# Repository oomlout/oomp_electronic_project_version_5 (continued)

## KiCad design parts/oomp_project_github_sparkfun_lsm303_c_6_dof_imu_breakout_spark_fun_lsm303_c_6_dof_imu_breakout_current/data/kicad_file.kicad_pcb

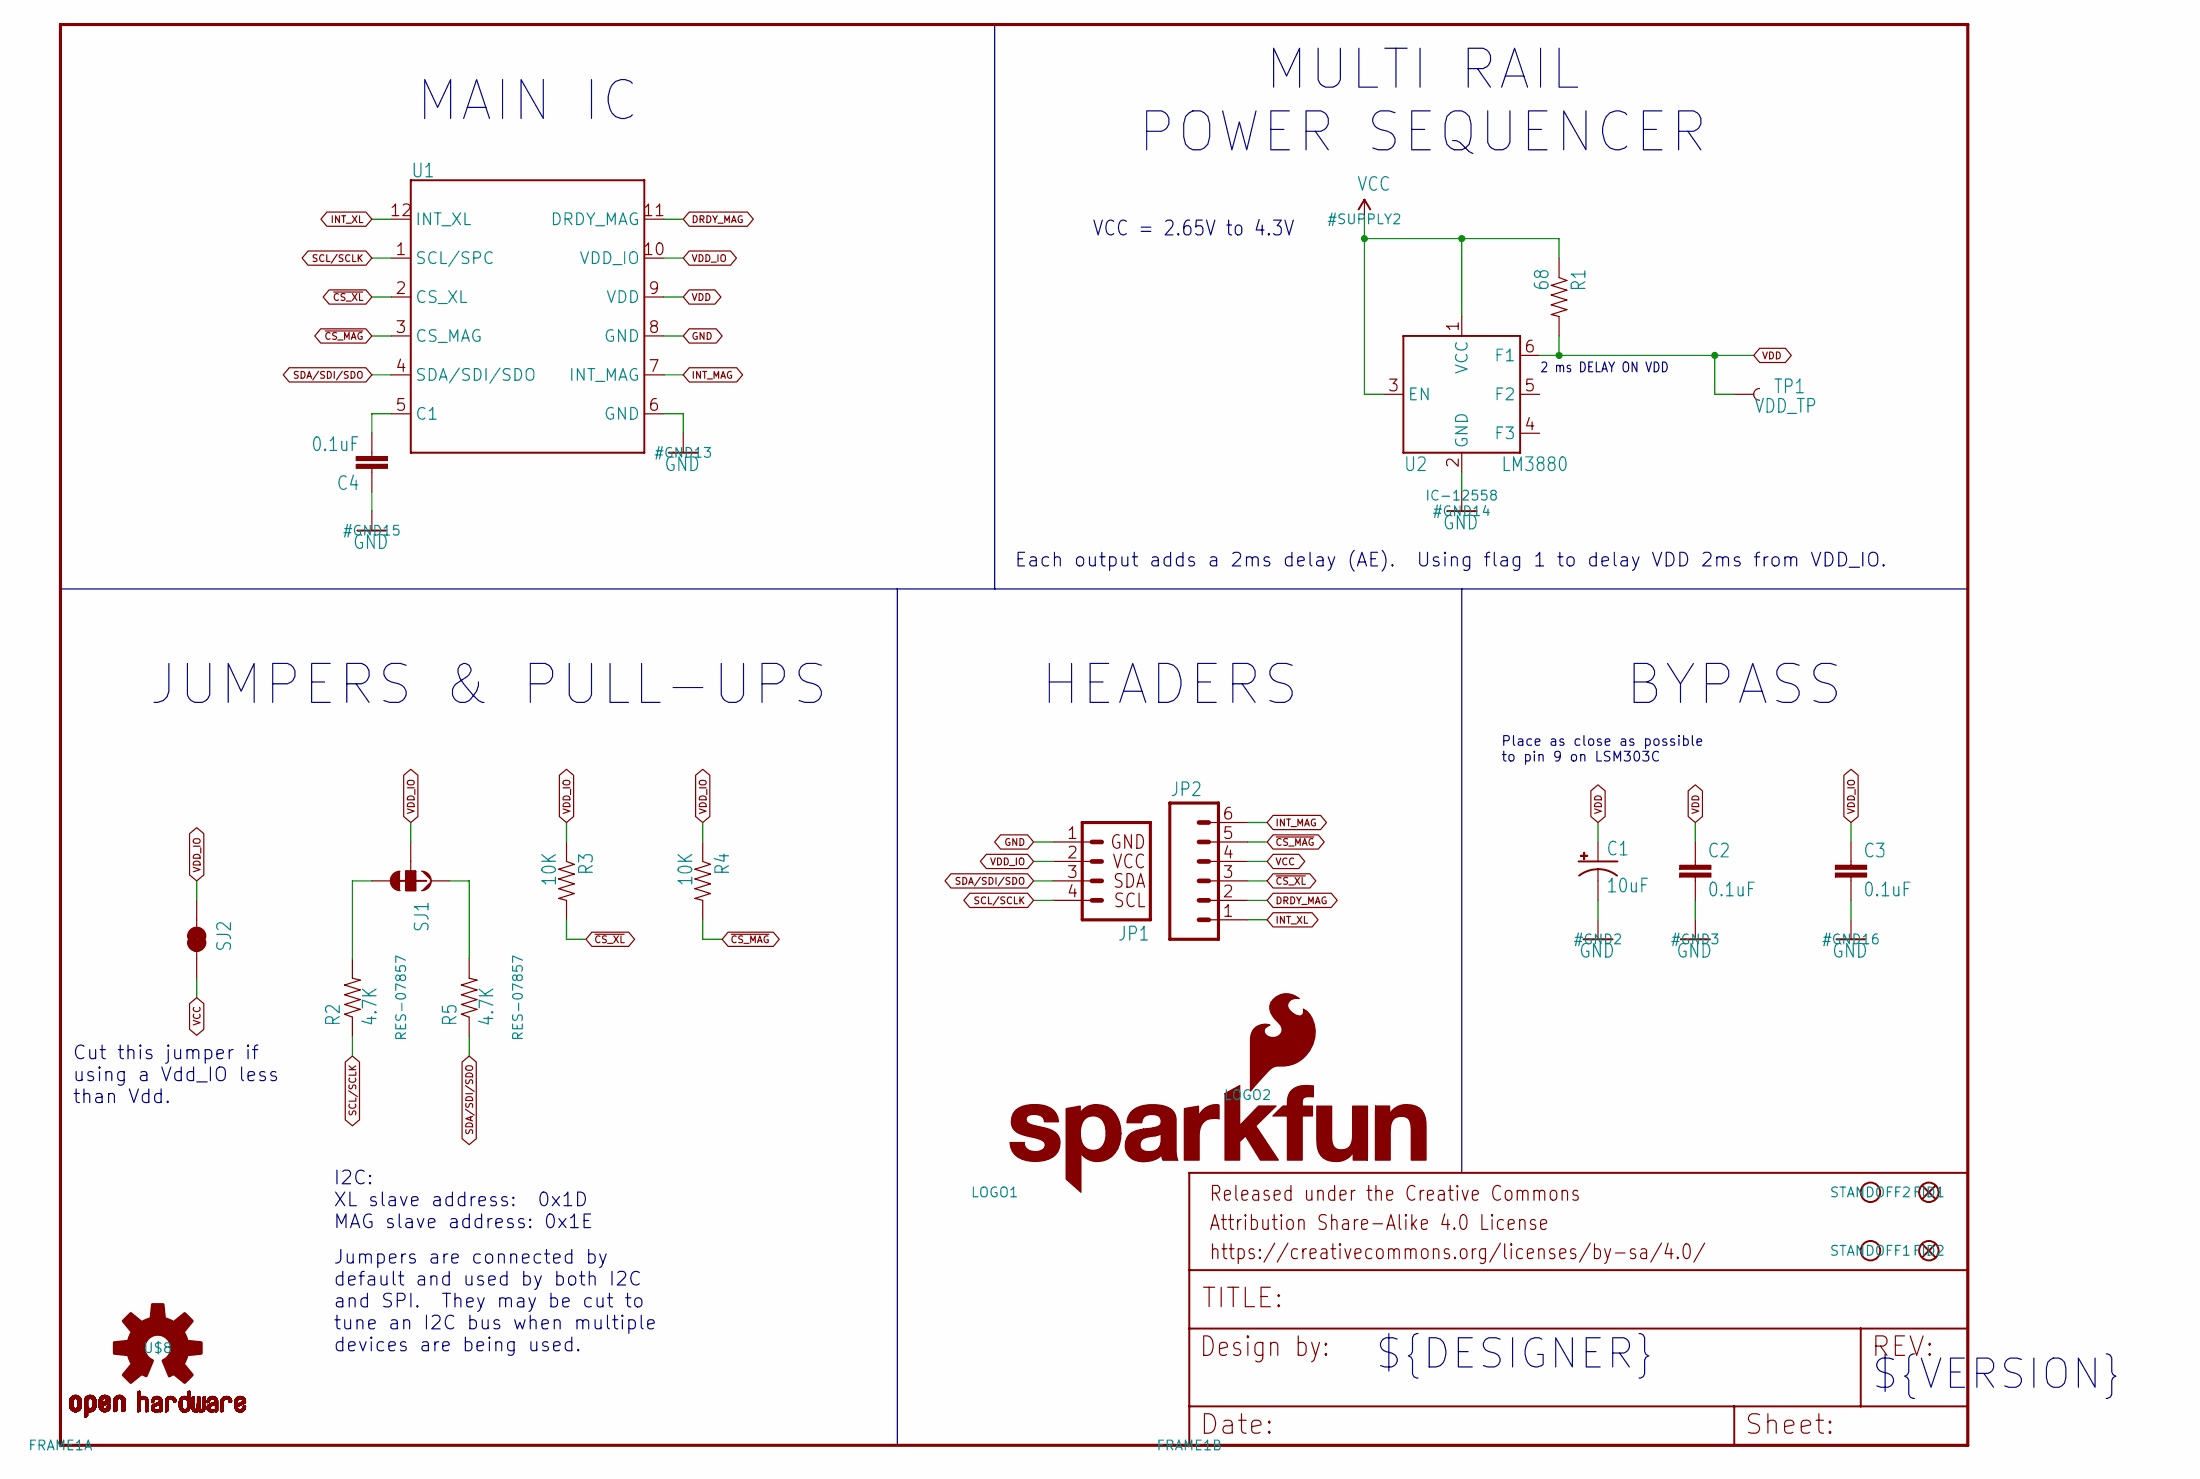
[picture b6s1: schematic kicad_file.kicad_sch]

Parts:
C1: 10uF; EIA3216
C2, C3, C4: 0.1uF; 0603-CAP
FID1, FID2: FIDUCIAL1X2; FIDUCIAL-1X2
FRAME1: FRAME-LETTER; CREATIVE_COMMONS
JP1: I2C_STANDARD; 1X04
JP2: M06SILK_FEMALE_PTH; 1X06
LOGO1: SFE_LOGO_NAME.1_INCH; SFE_LOGO_NAME_.1
LOGO2: SFE_LOGO_FLAME.1EXP; SFE_LOGO_FLAME_COPPER_EXPOSED_.1
R1: 68; 0603-RES
R2, R5: 4.7K; 0603-RES
R3, R4: 10K; 0603-RES
SJ1: JUMPER-PAD-3-NC_BY_TRACE; PAD-JUMPER-3-3OF3_NC_BY_TRACE_YES_SILK_FULL_BOX
SJ2: JUMPER-PAD-2-NC_BY_TRACE; PAD-JUMPER-2-NC_BY_TRACE_YES_SILK
STANDOFF1, STANDOFF2: STAND-OFF
TP1: VDD_TP; TP_15TH
U1: LSM303C; LGA-12
U2: LM3880; SOT23-6
U$8: OSHW-LOGOS; OSHW-LOGO-S

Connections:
DRDY_MAG: JP2.2, U1.11 (DRDY_MAG)
GND: C1.C (-), C2.2, C3.2, C4.1, JP1.1, U1.6 (GND), U1.8 (GND), U2.2 (GND)
I2C-UP: R5.2, SJ1.1
INT_MAG: JP2.6, U1.7 (INT_MAG)
INT_XL: JP2.1, U1.12 (INT_XL)
unnamed: C4.2, U1.5 (C1)
unnamed: R2.2, SJ1.3
SCL/SCLK: JP1.4, R2.1, U1.1 (SCL/SPC)
SDA/SDI/SDO: JP1.3, R5.1, U1.4 (SDA/SDI/SDO)
VCC: JP2.4, R1.1, SJ2.2, U2.1 (VCC), U2.3 (EN)
VDD: C1.A (+), C2.1, R1.2, TP1.P$1, U1.9 (VDD), U2.6 (F1)
VDD_IO: C3.1, JP1.2, R3.1, R4.1, SJ1.2, SJ2.1, U1.10 (VDD_IO)
~CS_MAG: JP2.5, R4.2, U1.3 (CS_MAG)
~CS_XL: JP2.3, R3.2, U1.2 (CS_XL)

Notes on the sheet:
JUMPERS & PULL-UPS
MULTI RAIL POWER SEQUENCER
I2C: XL slave address: 0x1D MAG slave address: 0x1E
2 ms DELAY ON VDD
MAIN IC
Jumpers are connected by default and used by both I2C and SPI. They may be cut to tune an I2C bus when multiple devices are being used.
Place as close as possible to pin 9 on LSM303C
HEADERS
${VERSION}
VCC = 2.65V to 4.3V
BYPASS
${DESIGNER}
Each output adds a 2ms delay (AE). Using flag 1 to delay VDD 2ms from VDD_IO.
Cut this jumper if using a Vdd_IO less than Vdd.

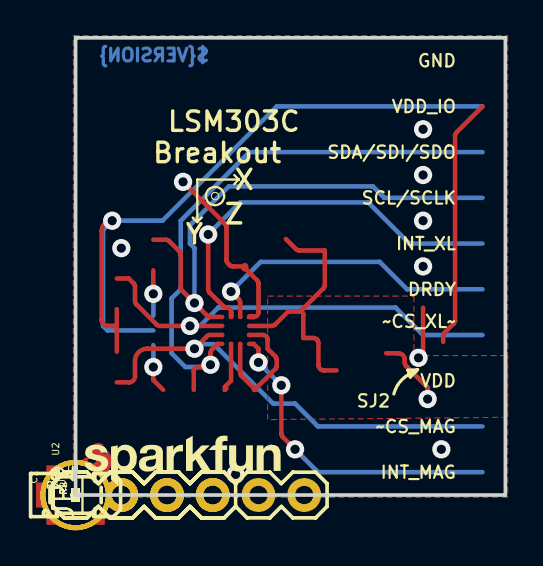
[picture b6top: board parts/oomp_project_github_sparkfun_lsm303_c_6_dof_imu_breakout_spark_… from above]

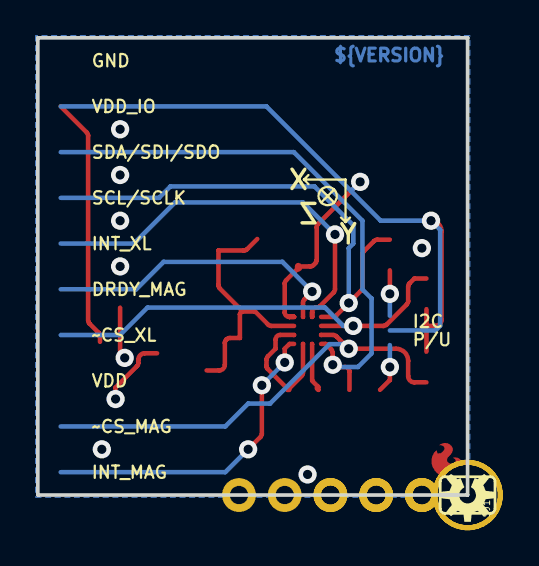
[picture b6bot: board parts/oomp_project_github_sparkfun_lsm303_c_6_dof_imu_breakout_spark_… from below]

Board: 2 copper layers, 23.9 x 25.4 mm, 24 parts (2 on the bottom side), 14 nets.

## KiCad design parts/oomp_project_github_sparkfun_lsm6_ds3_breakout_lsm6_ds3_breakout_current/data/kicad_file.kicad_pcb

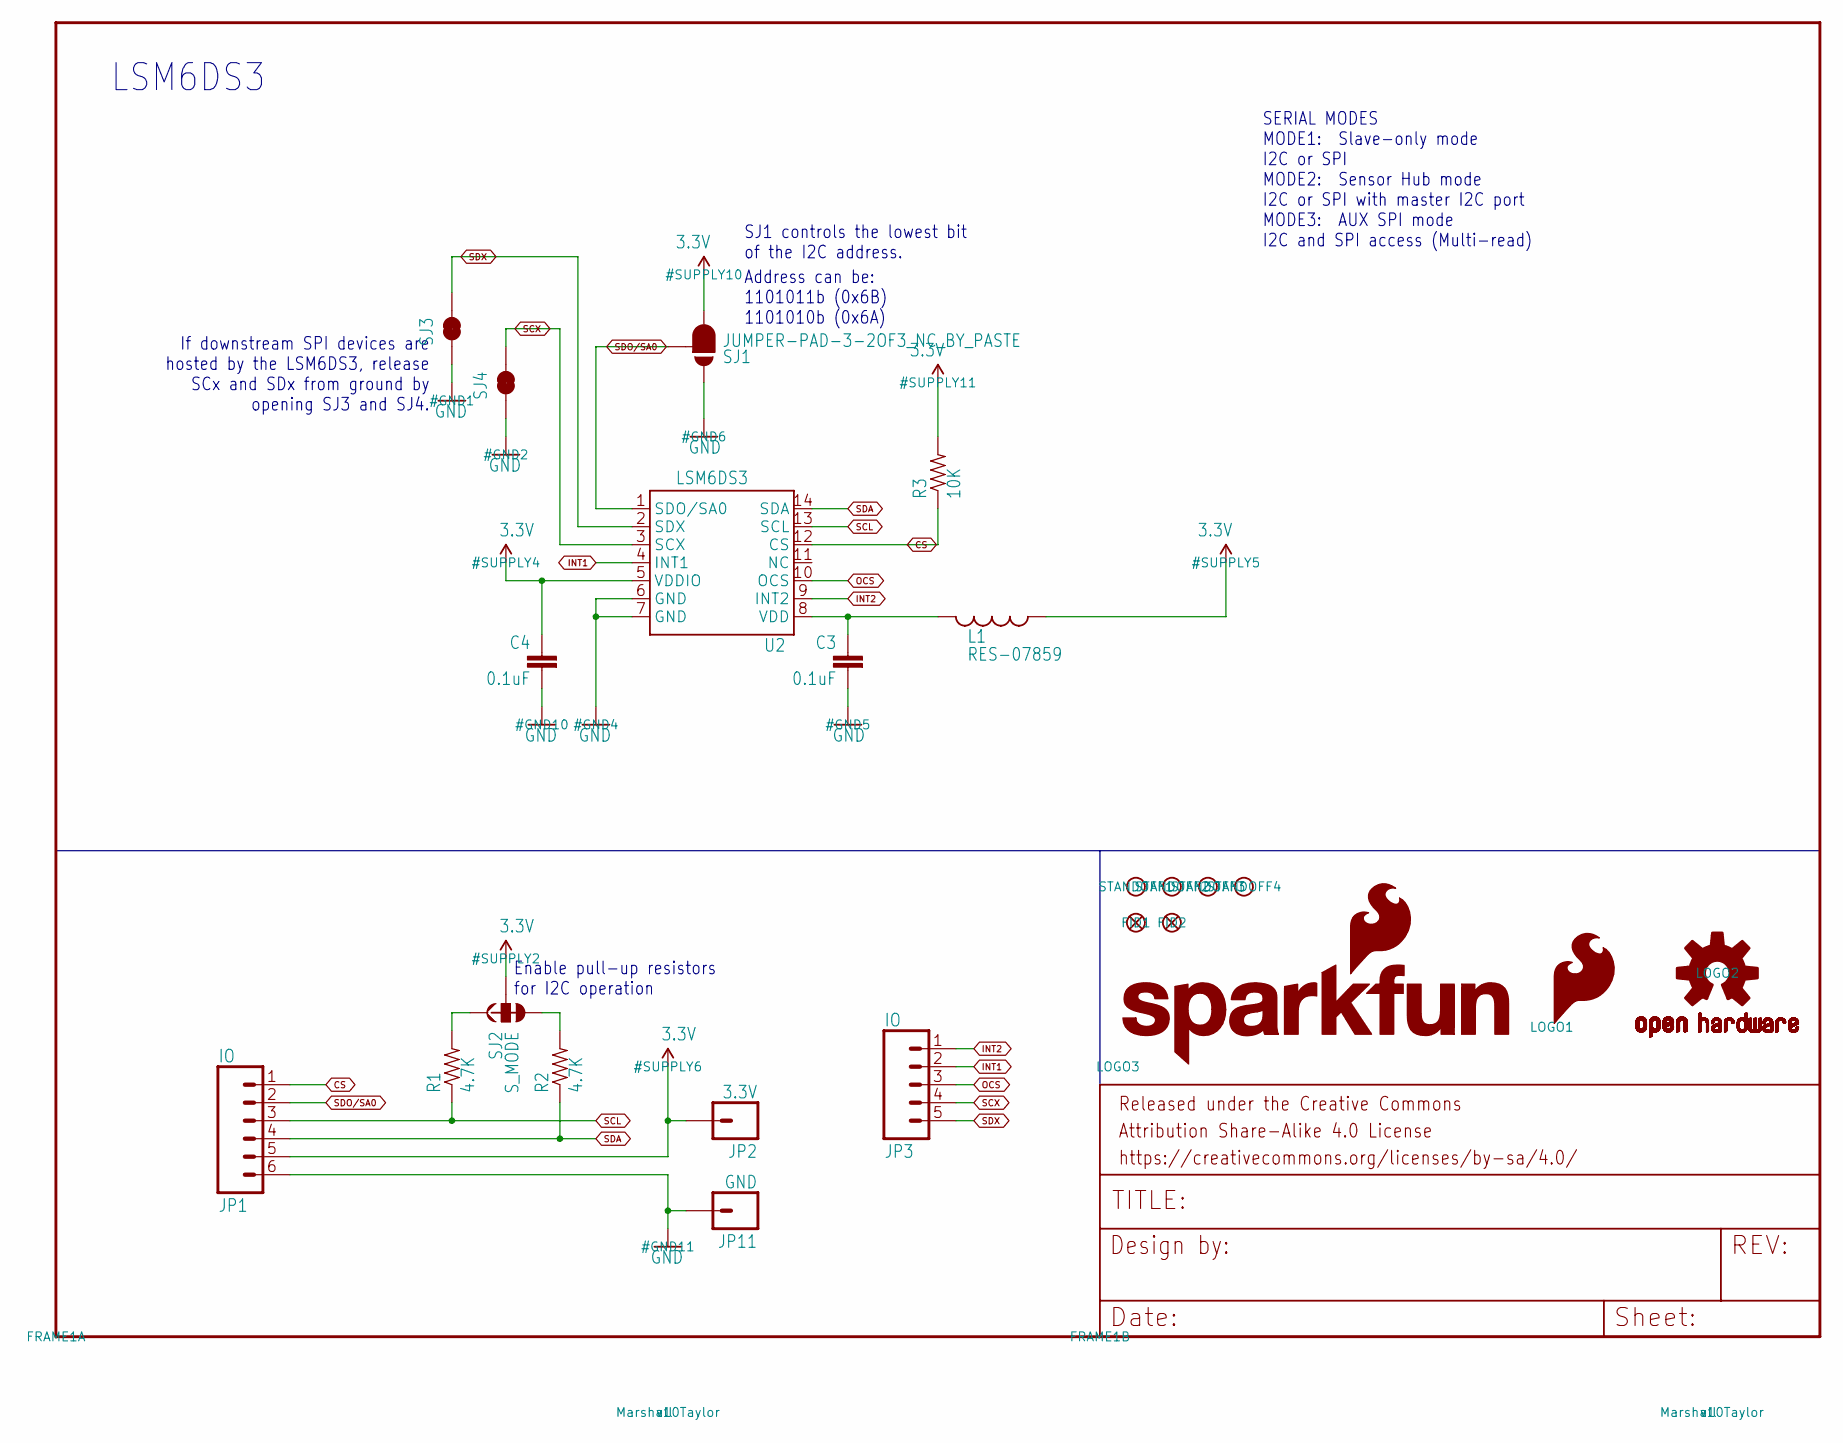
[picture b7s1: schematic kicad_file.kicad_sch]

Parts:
C3, C4: 0.1uF; 0603-CAP
FID1, FID2: FIDUCIAL1X2; FIDUCIAL-1X2
FRAME1: FRAME-LETTER; CREATIVE_COMMONS
JP1: IO; 1X06_NO_SILK_YES_STOP
JP2: 3.3V; 1X01_NO_SILK
JP3: IO; 1X05
JP11: GND; 1X01_NO_SILK
L1: RES-07859; 0603
LOGO1: SFE_LOGO_FLAME.2_INCH; SFE_LOGO_FLAME_.2
LOGO2: OSHW-LOGOS; OSHW-LOGO-S
LOGO3: SFE_LOGO_NAME_FLAME.1_INCH; SFE_LOGO_NAME_FLAME_.1
R1, R2: 4.7K; 0603-RES
R3: 10K; 0603-RES
SJ1: JUMPER-PAD-3-2OF3_NC_BY_PASTE; PAD-JUMPER-3-2OF3_NC_BY_PASTE_YES_SILK_FULL_BOX
SJ2: S_MODE; PAD-JUMPER-3-3OF3_NC_BY_TRACE_YES_SILK_FULL_BOX
SJ3, SJ4: JUMPER-PAD-2-NC_BY_TRACE; PAD-JUMPER-2-NC_BY_TRACE_YES_SILK
STANDOFF1, STANDOFF2, STANDOFF3, STANDOFF4: STAND-OFF
U2: LSM6DS3; LGA14L_DOT_INDICATOR

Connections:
3.3V: C4.1, JP1.5, JP2.1, L1.1, R3.2, SJ1.3, SJ2.2, U2.5 (VDDIO)
CS: JP1.1, R3.1, U2.12 (CS)
GND: C3.2, C4.2, JP1.6, JP11.1, SJ1.1, SJ3.1, SJ4.1, U2.6 (GND), U2.7 (GND)
INT1: JP3.2, U2.4 (INT1)
INT2: JP3.1, U2.9 (INT2)
unnamed: R1.2, SJ2.1
unnamed: R2.2, SJ2.3
OCS: JP3.3, U2.10 (OCS)
SCL: JP1.3, R1.1, U2.13 (SCL)
SCX: JP3.4, SJ4.2, U2.3 (SCX)
SDA: JP1.4, R2.1, U2.14 (SDA)
SDO/SA0: JP1.2, SJ1.2, U2.1 (SDO/SA0)
SDX: JP3.5, SJ3.2, U2.2 (SDX)
VDD: C3.1, L1.2, U2.8 (VDD)

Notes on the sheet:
Address can be: 1101011b (0x6B) 1101010b (0x6A)
SERIAL MODES MODE1: Slave-only mode I2C or SPI MODE2: Sensor Hub mode I2C or SPI with master I2C port MODE3: AUX SPI mode I2C and SPI access (Multi-read)
If downstream SPI devices are hosted by the LSM6DS3, release SCx and SDx from ground by opening SJ3 and SJ4.
SJ1 controls the lowest bit of the I2C address.
Enable pull-up resistors for I2C operation
LSM6DS3

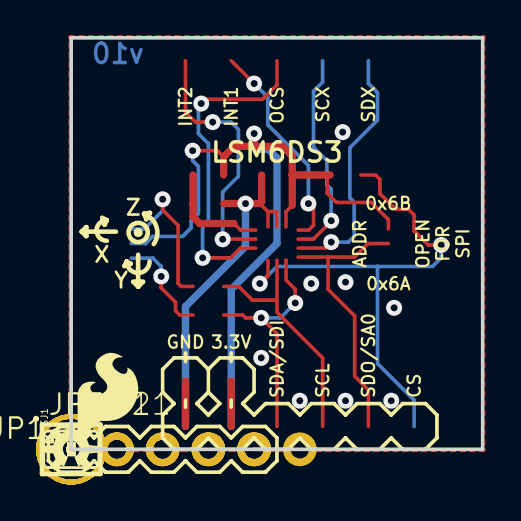
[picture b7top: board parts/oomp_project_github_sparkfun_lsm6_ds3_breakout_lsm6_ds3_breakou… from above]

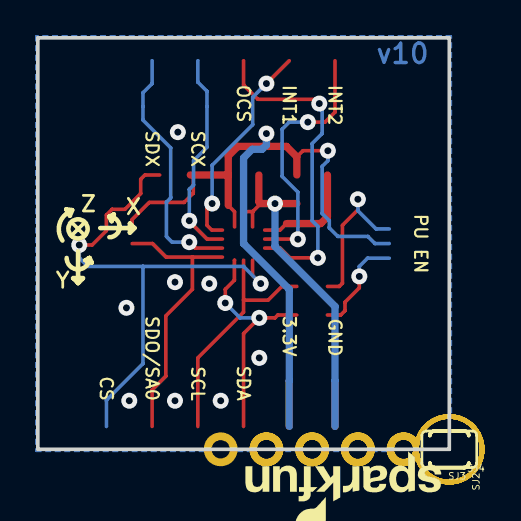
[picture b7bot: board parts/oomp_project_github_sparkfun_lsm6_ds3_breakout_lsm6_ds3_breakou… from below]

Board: 2 copper layers, 22.9 x 22.9 mm, 25 parts (4 on the bottom side), 14 nets.

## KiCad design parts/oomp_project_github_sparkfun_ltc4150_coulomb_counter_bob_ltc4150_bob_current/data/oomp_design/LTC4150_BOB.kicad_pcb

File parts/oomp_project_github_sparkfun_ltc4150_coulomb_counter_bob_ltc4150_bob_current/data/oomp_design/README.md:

# OOMP KiCad design copy

Open `LTC4150_BOB.kicad_pro` (or the `.kicad_pcb` / `.kicad_sch`) in KiCad. Local OOMP libraries are under `libraries/`. Original inputs are preserved in [../original/](../original/).

Only verified unchanged installed KiCad defaults were renamed. Modified, custom, unmatched and unavailable items remain unchanged. Soldering variants are never swapped during conversion. Existing pad coordinates, nets and UUIDs are preserved.

See [conversion_report.yaml](conversion_report.yaml) for every conversion and skip. Copy this directory before editing; regeneration refuses to overwrite edited design files.

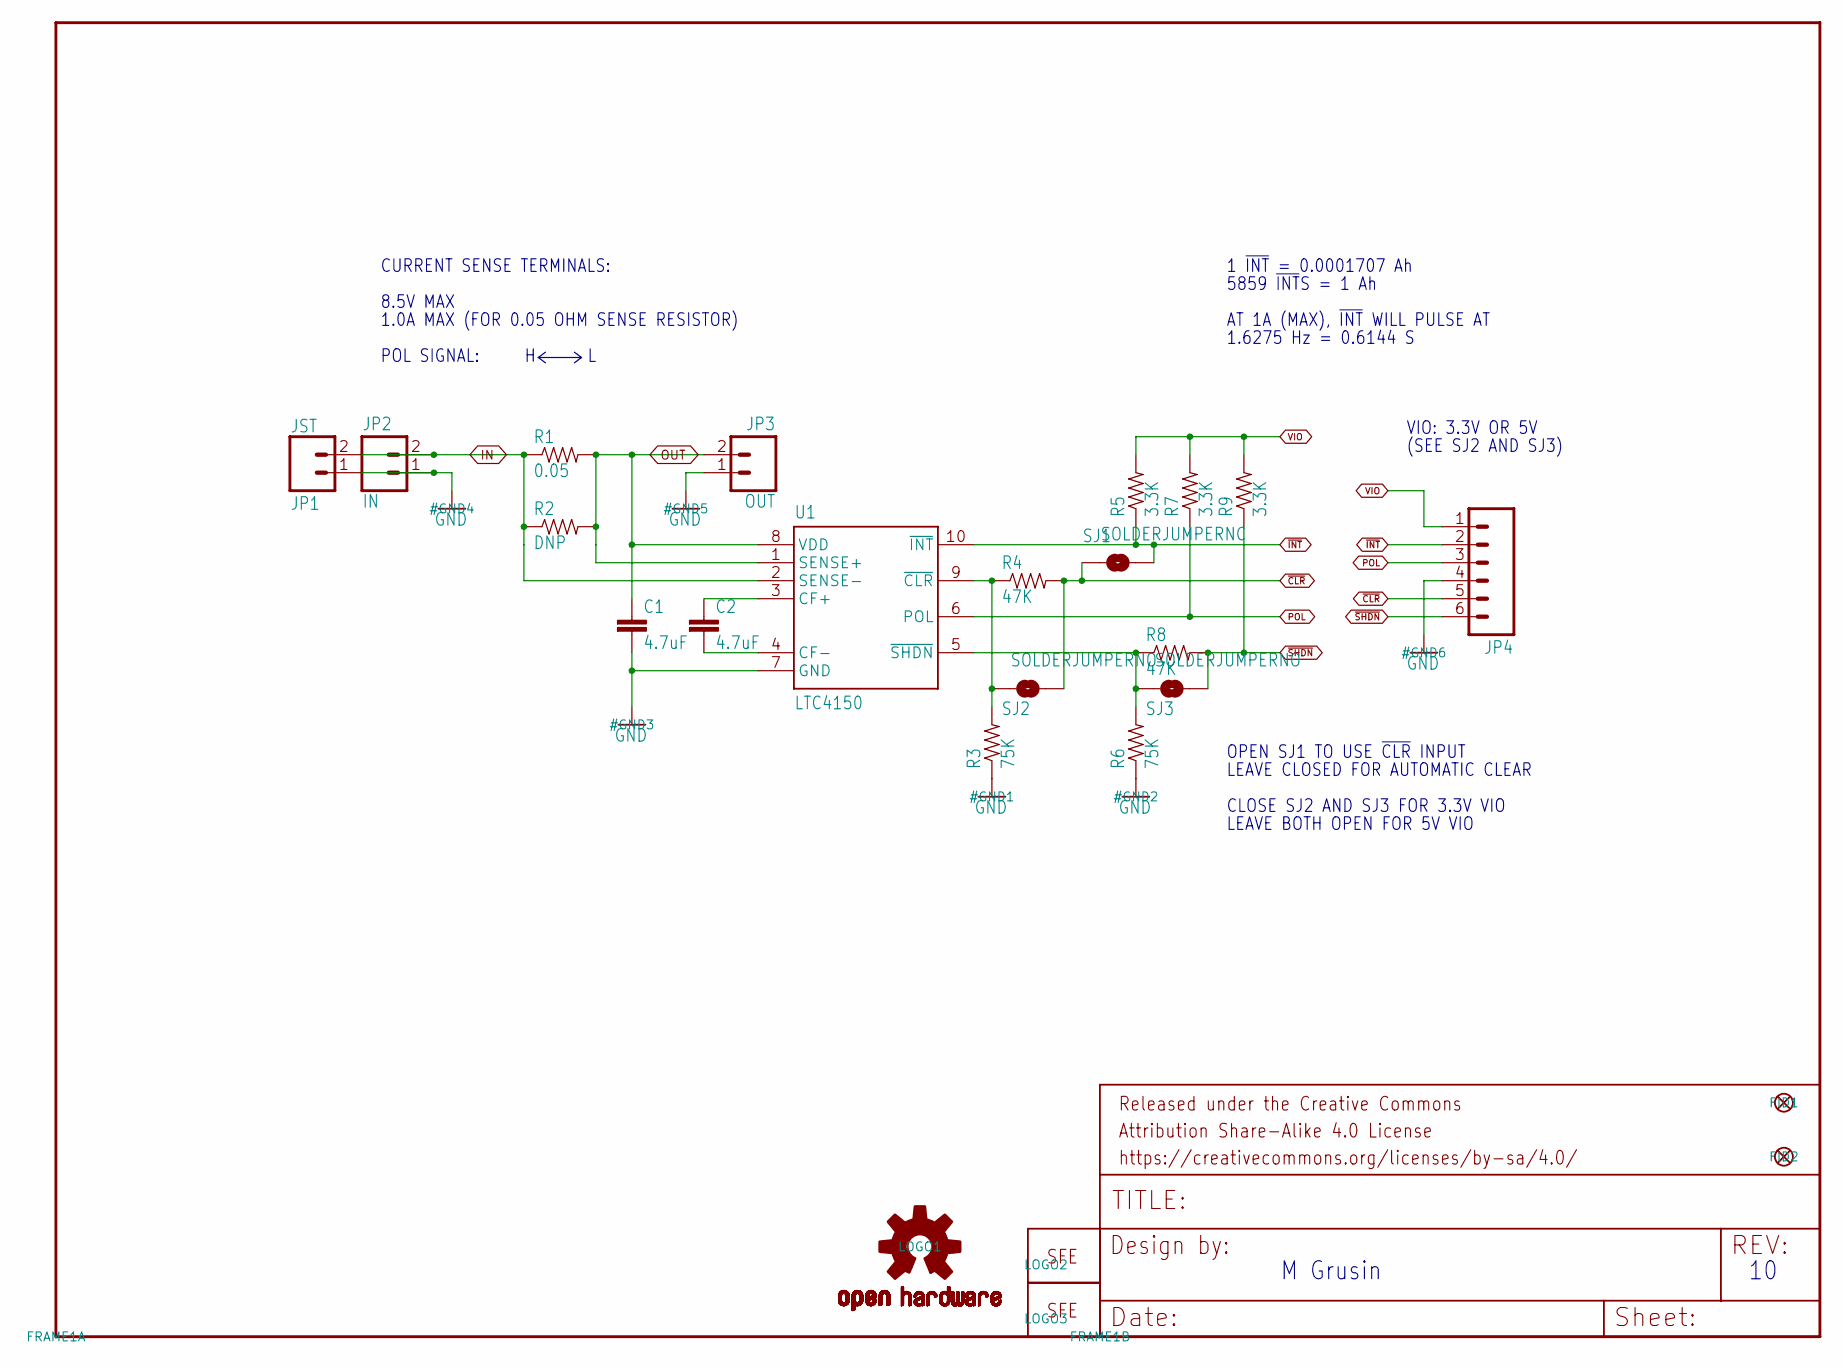
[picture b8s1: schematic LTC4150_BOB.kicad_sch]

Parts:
C1, C2: 4.7uF; 0603-CAP
FID1, FID2: FIDUCIAL1X2; FIDUCIAL-1X2
FRAME1: FRAME-LETTER; CREATIVE_COMMONS
JP1: JST; JST-2-SMD
JP2: IN; 1X02
JP3: OUT; 1X02
JP4: M06SIP; 1X06
LOGO1: OSHW-LOGOS; OSHW-LOGO-S
LOGO2: LOGO-SFENW2; SFE-NEW-WEB
LOGO3: LOGO-SFESK; SFE-LOGO-FLAME
R1: 0.05; 1206
R2: DNP; AXIAL-0.3
R3, R6: 75K; 0603-RES
R4, R8: 47K; 0603-RES
R5, R7, R9: 3.3K; 0603-RES
SJ1: SOLDERJUMPERNC; SJ_2S
SJ2, SJ3: SOLDERJUMPERNO; SJ_2S-NO
U1: LTC4150; MSOP10

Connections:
GND: C1.2, JP1.1 (2), JP2.1, JP3.1, JP4.4, R3.1, R6.1, U1.7 (GND)
IN: JP1.2 (1), JP2.2, R1.1, R2.P$1 (1), U1.2 (SENSE-)
unnamed: R3.2, R4.1, SJ2.1, U1.9 (~CLR)
unnamed: C2.1, U1.3 (CF+)
unnamed: C2.2, U1.4 (CF-)
unnamed: R6.2, R8.1, SJ3.1, U1.5 (~SHDN)
OUT: C1.1, JP3.2, R1.2, R2.P$2 (2), U1.1 (SENSE+), U1.8 (VDD)
POL: JP4.3, R7.1, U1.6 (POL)
VIO: JP4.1, R5.2, R7.2, R9.2
~CLR: JP4.5, R4.2, SJ1.1, SJ2.2
~INT: JP4.2, R5.1, SJ1.2, U1.10 (~INT)
~SHDN: JP4.6, R8.2, R9.1, SJ3.2

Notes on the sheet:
LEAVE BOTH OPEN FOR 5V VIO
(SEE SJ2 AND SJ3)
CURRENT SENSE TERMINALS:
CLOSE SJ2 AND SJ3 FOR 3.3V VIO
OPEN SJ1 TO USE ~{CLR} INPUT
1 ~{INT} = 0.0001707 Ah
1.6275 Hz = 0.6144 S
AT 1A (MAX), ~{INT} WILL PULSE AT
M Grusin
8.5V MAX
5859 ~{INT}S = 1 Ah
1.0A MAX (FOR 0.05 OHM SENSE RESISTOR)
LEAVE CLOSED FOR AUTOMATIC CLEAR
VIO: 3.3V OR 5V
POL SIGNAL:

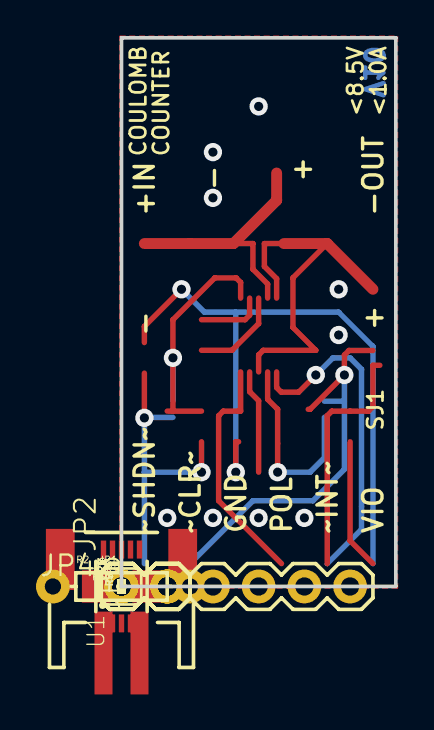
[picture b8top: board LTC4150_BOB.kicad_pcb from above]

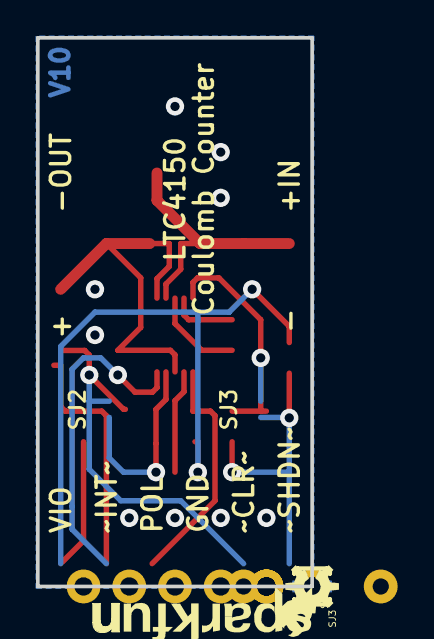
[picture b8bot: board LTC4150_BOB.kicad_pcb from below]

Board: 2 copper layers, 15.2 x 30.5 mm, 25 parts (5 on the bottom side), 12 nets.
